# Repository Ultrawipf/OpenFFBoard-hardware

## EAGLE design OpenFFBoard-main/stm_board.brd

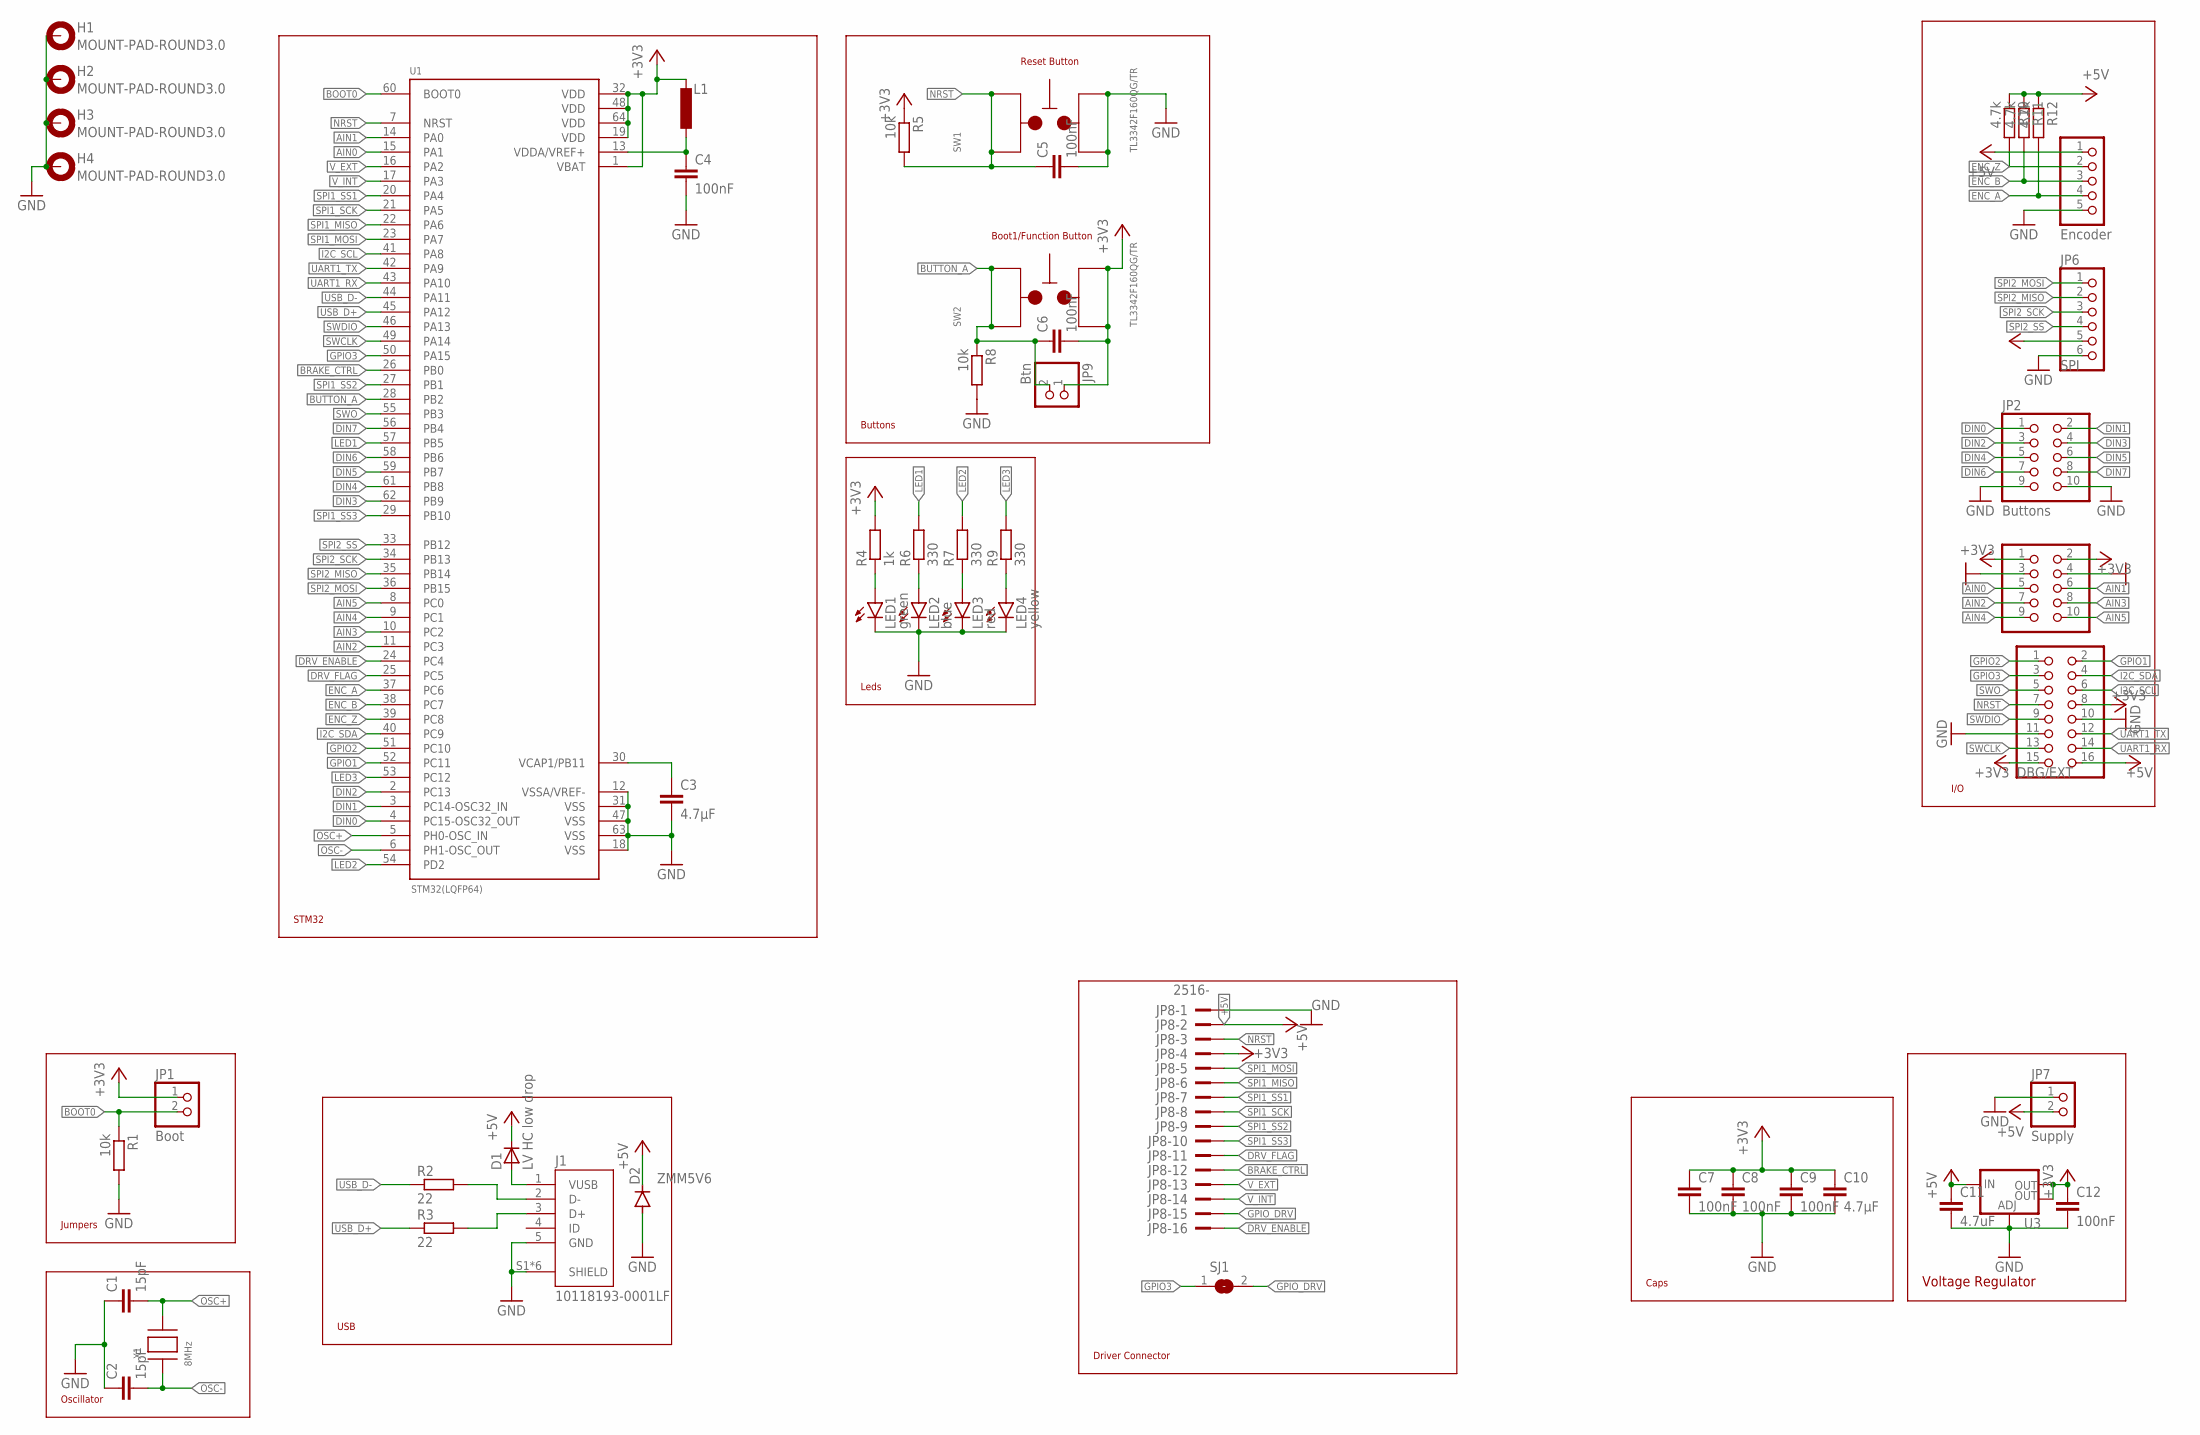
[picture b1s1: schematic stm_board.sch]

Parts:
C1, C2: 15pF; C0603
C3, C10: 4.7µF; C0805
C4, C5, C6, C7, C8, C9, C12: 100nF; C0603
C11: 4.7uF; C0805
D1: LV HC low drop; SMADIODE
D2: ZMM5V6; MINIMELF
H1, H2, H3, H4: MOUNT-PAD-ROUND3.0; 3,0-PAD
J1: 10118193-0001LF; FCI_10118193-0001LF
JP1: Boot; 1X02
JP2: Buttons; 2X05
JP3: Analog; 2X05
JP4: DBG/EXT; 2X08
JP5: Encoder; 1X05
JP6: SPI; 1X06
JP7: Supply; 1X02
JP8: 2516-; PAK100/2500-16
JP9: Btn; 1X02
L1: 2.2µH; L2012C
LED1: green; CHIPLED_0805
LED2: blue; CHIPLED_0805
LED3: red; CHIPLED_0805
LED4: yellow; CHIPLED_0805
R1, R5, R8: 10k; R0603
R2, R3: 22; R0603
R4: 1k; R0603
R6, R7, R9: 330; R0603
R10, R11, R12: 4.7k; R0603
SJ1: SJ
SW1, SW2: TL3342F160QG/TR
U1: STM32(LQFP64); QFP50P1200X1200X160-64N
U3: V_REG_LM1117SOT223; SOT223
X1: 8MHz; NX5032

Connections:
+3V3: C6.2, C7.1, C8.1, C9.1, C10.1, C12.1, JP1.1, JP3.1, JP3.2, JP4.8, JP4.15, JP6.5, JP8.4, JP9.1, L1.1, R4.2, R5.1, SW2.1, SW2.2, U1.1 (VBAT), U1.19 (VDD), U1.32 (VDD), U1.48 (VDD), U1.64 (VDD), U3.2 (OUT), U3.4 (OUT)
+5V: C11.1, D1.C, D2.C, JP4.16, JP5.1, JP7.2, JP8.2, R10.1, R11.1, R12.1, U3.3 (IN)
AIN0: JP3.5, U1.15 (PA1)
AIN1: JP3.6, U1.14 (PA0)
AIN2: JP3.7, U1.11 (PC3)
AIN3: JP3.8, U1.10 (PC2)
AIN4: JP3.9, U1.9 (PC1)
AIN5: JP3.10, U1.8 (PC0)
BOOT0: JP1.2, R1.1, U1.60 (BOOT0)
BRAKE_CTRL: JP8.12, U1.26 (PB0)
BUTTON_A: C6.1, JP9.2, R8.1, SW2.3, SW2.4, U1.28 (PB2)
DIN0: JP2.1, U1.4 (PC15-OSC32_OUT)
DIN1: JP2.2, U1.3 (PC14-OSC32_IN)
DIN2: JP2.3, U1.2 (PC13)
DIN3: JP2.4, U1.62 (PB9)
DIN4: JP2.5, U1.61 (PB8)
DIN5: JP2.6, U1.59 (PB7)
DIN6: JP2.7, U1.58 (PB6)
DIN7: JP2.8, U1.56 (PB4)
DRV_ENABLE: JP8.16, U1.24 (PC4)
DRV_FLAG: JP8.11, U1.25 (PC5)
ENC_A: JP5.4, R12.2, U1.37 (PC6)
ENC_B: JP5.3, R11.2, U1.38 (PC7)
ENC_Z: JP5.2, R10.2, U1.39 (PC8)
GND: C1.1, C2.1, C3.2, C4.2, C5.2, C7.2, C8.2, C9.2, C10.2, C11.2, C12.2, D2.A, H1.B3,0, H2.B3,0, H3.B3,0, H4.B3,0, J1.5 (GND), J1.S1 (SHIELD), J1.S2 (SHIELD), J1.S3 (SHIELD), J1.S4 (SHIELD), J1.S5 (SHIELD), J1.S6 (SHIELD), JP2.9, JP2.10, JP3.3, JP3.4, JP4.10, JP4.11, JP5.5, JP6.6, JP7.1, JP8.1, LED1.C, LED2.C, LED3.C, LED4.C, R1.2, R8.2, SW1.1, SW1.2, U1.12 (VSSA/VREF-), U1.18 (VSS), U1.31 (VSS), U1.47 (VSS), U1.63 (VSS), U3.1 (ADJ)
GPIO1: JP4.2, U1.52 (PC11)
GPIO2: JP4.1, U1.51 (PC10)
GPIO3: JP4.3, SJ1.1, U1.50 (PA15)
GPIO_DRV: JP8.15, SJ1.2
I2C_SCL: JP4.6, U1.41 (PA8)
I2C_SDA: JP4.4, U1.40 (PC9)
LED1: R6.2, U1.57 (PB5)
LED2: R7.2, U1.54 (PD2)
LED3: R9.2, U1.53 (PC12)
unnamed: D1.A, J1.1 (VUSB)
unnamed: LED4.A, R9.1
unnamed: C4.1, L1.2, U1.13 (VDDA/VREF+)
unnamed: C3.1, U1.30 (VCAP1/PB11)
unnamed: J1.2 (D-), R2.2
unnamed: J1.3 (D+), R3.2
unnamed: LED1.A, R4.1
unnamed: LED2.A, R6.1
unnamed: LED3.A, R7.1
NRST: C5.1, JP4.7, JP8.3, R5.2, SW1.3, SW1.4, U1.7 (NRST)
OSC+: C1.2, U1.5 (PH0-OSC_IN), X1.P$2
OSC-: C2.2, U1.6 (PH1-OSC_OUT), X1.P$1
SPI1_MISO: JP8.6, U1.22 (PA6)
SPI1_MOSI: JP8.5, U1.23 (PA7)
SPI1_SCK: JP8.8, U1.21 (PA5)
SPI1_SS1: JP8.7, U1.20 (PA4)
SPI1_SS2: JP8.9, U1.27 (PB1)
SPI1_SS3: JP8.10, U1.29 (PB10)
SPI2_MISO: JP6.2, U1.35 (PB14)
SPI2_MOSI: JP6.1, U1.36 (PB15)
SPI2_SCK: JP6.3, U1.34 (PB13)
SPI2_SS: JP6.4, U1.33 (PB12)
SWCLK: JP4.13, U1.49 (PA14)
SWDIO: JP4.9, U1.46 (PA13)
SWO: JP4.5, U1.55 (PB3)
UART1_RX: JP4.14, U1.43 (PA10)
UART1_TX: JP4.12, U1.42 (PA9)
USB_D+: R3.1, U1.45 (PA12)
USB_D-: R2.1, U1.44 (PA11)
V_EXT: JP8.13, U1.16 (PA2)
V_INT: JP8.14, U1.17 (PA3)

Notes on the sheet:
Oscillator
USB
Boot1/Function Button
Reset Button
Buttons
Jumpers
Leds
Voltage Regulator
I/O
Driver Connector
Caps
STM32

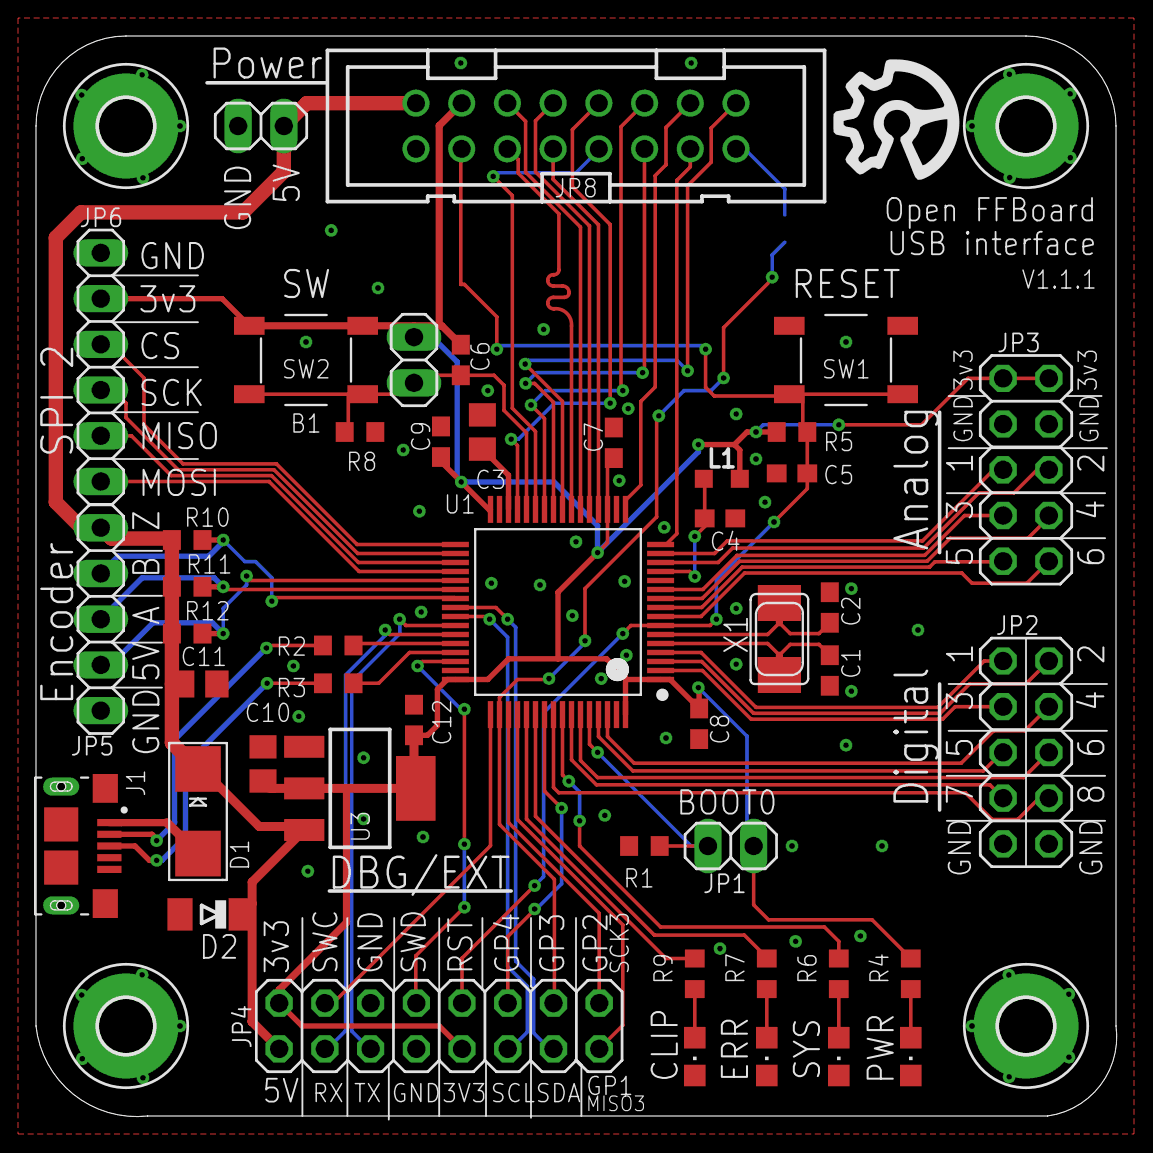
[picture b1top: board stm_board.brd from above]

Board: 2 copper layers, 60.0 x 60.0 mm, 51 parts (1 on the bottom side), 65 nets.

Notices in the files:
parts and their libraries:
SparkFun-IC-Power: Licensing: Creative Commons ShareAlike 4.0 International - https://creativecommons.org/licenses/by-sa/4.0
